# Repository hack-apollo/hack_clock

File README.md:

HACK LABS MatrixClock : https://www.youtube.com/watch?v=k0h2WS6Prsc&t=33s                                                                                
Author: HACK实验室                                                                                     
YouTube ID: HACK实验室, welcome to subscribe https://www.youtube.com/c/HACK实验室                                                        
HACK_CLOCK is a free download and may be used, modified, evaluated and
distributed without charge provided the user adheres to version three of the GNU
General Public License (GPL) and does not remove the copyright notice or this
text.  The GPL V3 text is available on the gnu.org web site
作者：HACK实验室                                                                                        
B站ID：HACK实验室  欢迎订阅 https://space.bilibili.com/395145107                                                                            
微信公众号：HACK实验室，开源资料唯一发布点，定期分享开源硬件以及有价值的技术文章，欢迎关注.

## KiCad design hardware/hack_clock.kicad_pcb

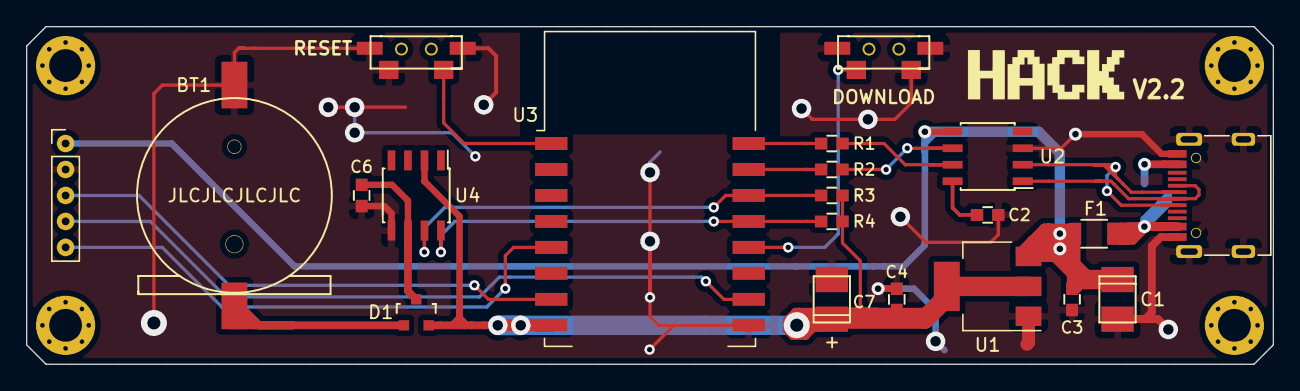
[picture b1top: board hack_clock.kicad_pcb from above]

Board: 2 copper layers, 96.0 x 26.0 mm, 23 parts (1 on the bottom side), 20 nets.

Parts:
BT1: BATTERY(M); CR1220-SMD
C1, C7: 100uF; TantalC_SizeT_3528
C2, C6: 0.1uF; 0603_C
C3, C4: 1uF; 0603_C
D1: BAT54C; SOT-23
F1: FUSE*; F_1206
J1: Conn_01x05_Male; PinHeader_1x05_P2.00mm_Vertical
J2: Jack-DC; BarrelJack_DCDC-SMT
P3: USB_C_Plug_USB2.0; USB-Type-C-NEW
P665: CON_1; CON1
R1, R2: RES(M); 0603_R
R3, R4: 10K; 0603_R
SW1, SW2: switch; SWITCH_PUSH
U1: AMS1117; SOT-223-3_TabPin2
U2: CH340N; SOP-8
U3: ESP-12; ESP-12S
U4: DS3231MZ+; SOP-8

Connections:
+3V3: C4.2, C7.1, D1.2, R3.2, R4.2, U1.2, U3.8, U4.2
+5V: C1.1, C3.2, F1.2, J1.1, U1.3, U2.5
/CLK: J1.5, U3.5
/CS: J1.4, U3.16
/DIN: J1.3, U3.7
/RXD: R1.2, U3.22
/SCL: R4.1, U3.19, U4.8
/SDA: R3.1, U3.20, U4.7
/TXD: R2.2, U3.21
/USB_D+: P3.A6, U2.1
/USB_D-: P3.A7, U2.2
GND: BT1.2, C1.2, C2.1, C3.1, C4.1, C6.1, C7.2, J1.2, J2.2, P3.A1, P3.S1, SW1.1, SW2.1, U1.1, U2.3, U3.15, U4.5
unnamed: BT1.1, D1.1
unnamed: C2.2, U2.8
unnamed: C6.2, D1.3, U4.6
unnamed: F1.1, J2.1, P3.A4
unnamed: R1.1, U2.7
unnamed: R2.1, U2.6
unnamed: SW1.2, U3.1
unnamed: SW2.2, U3.18

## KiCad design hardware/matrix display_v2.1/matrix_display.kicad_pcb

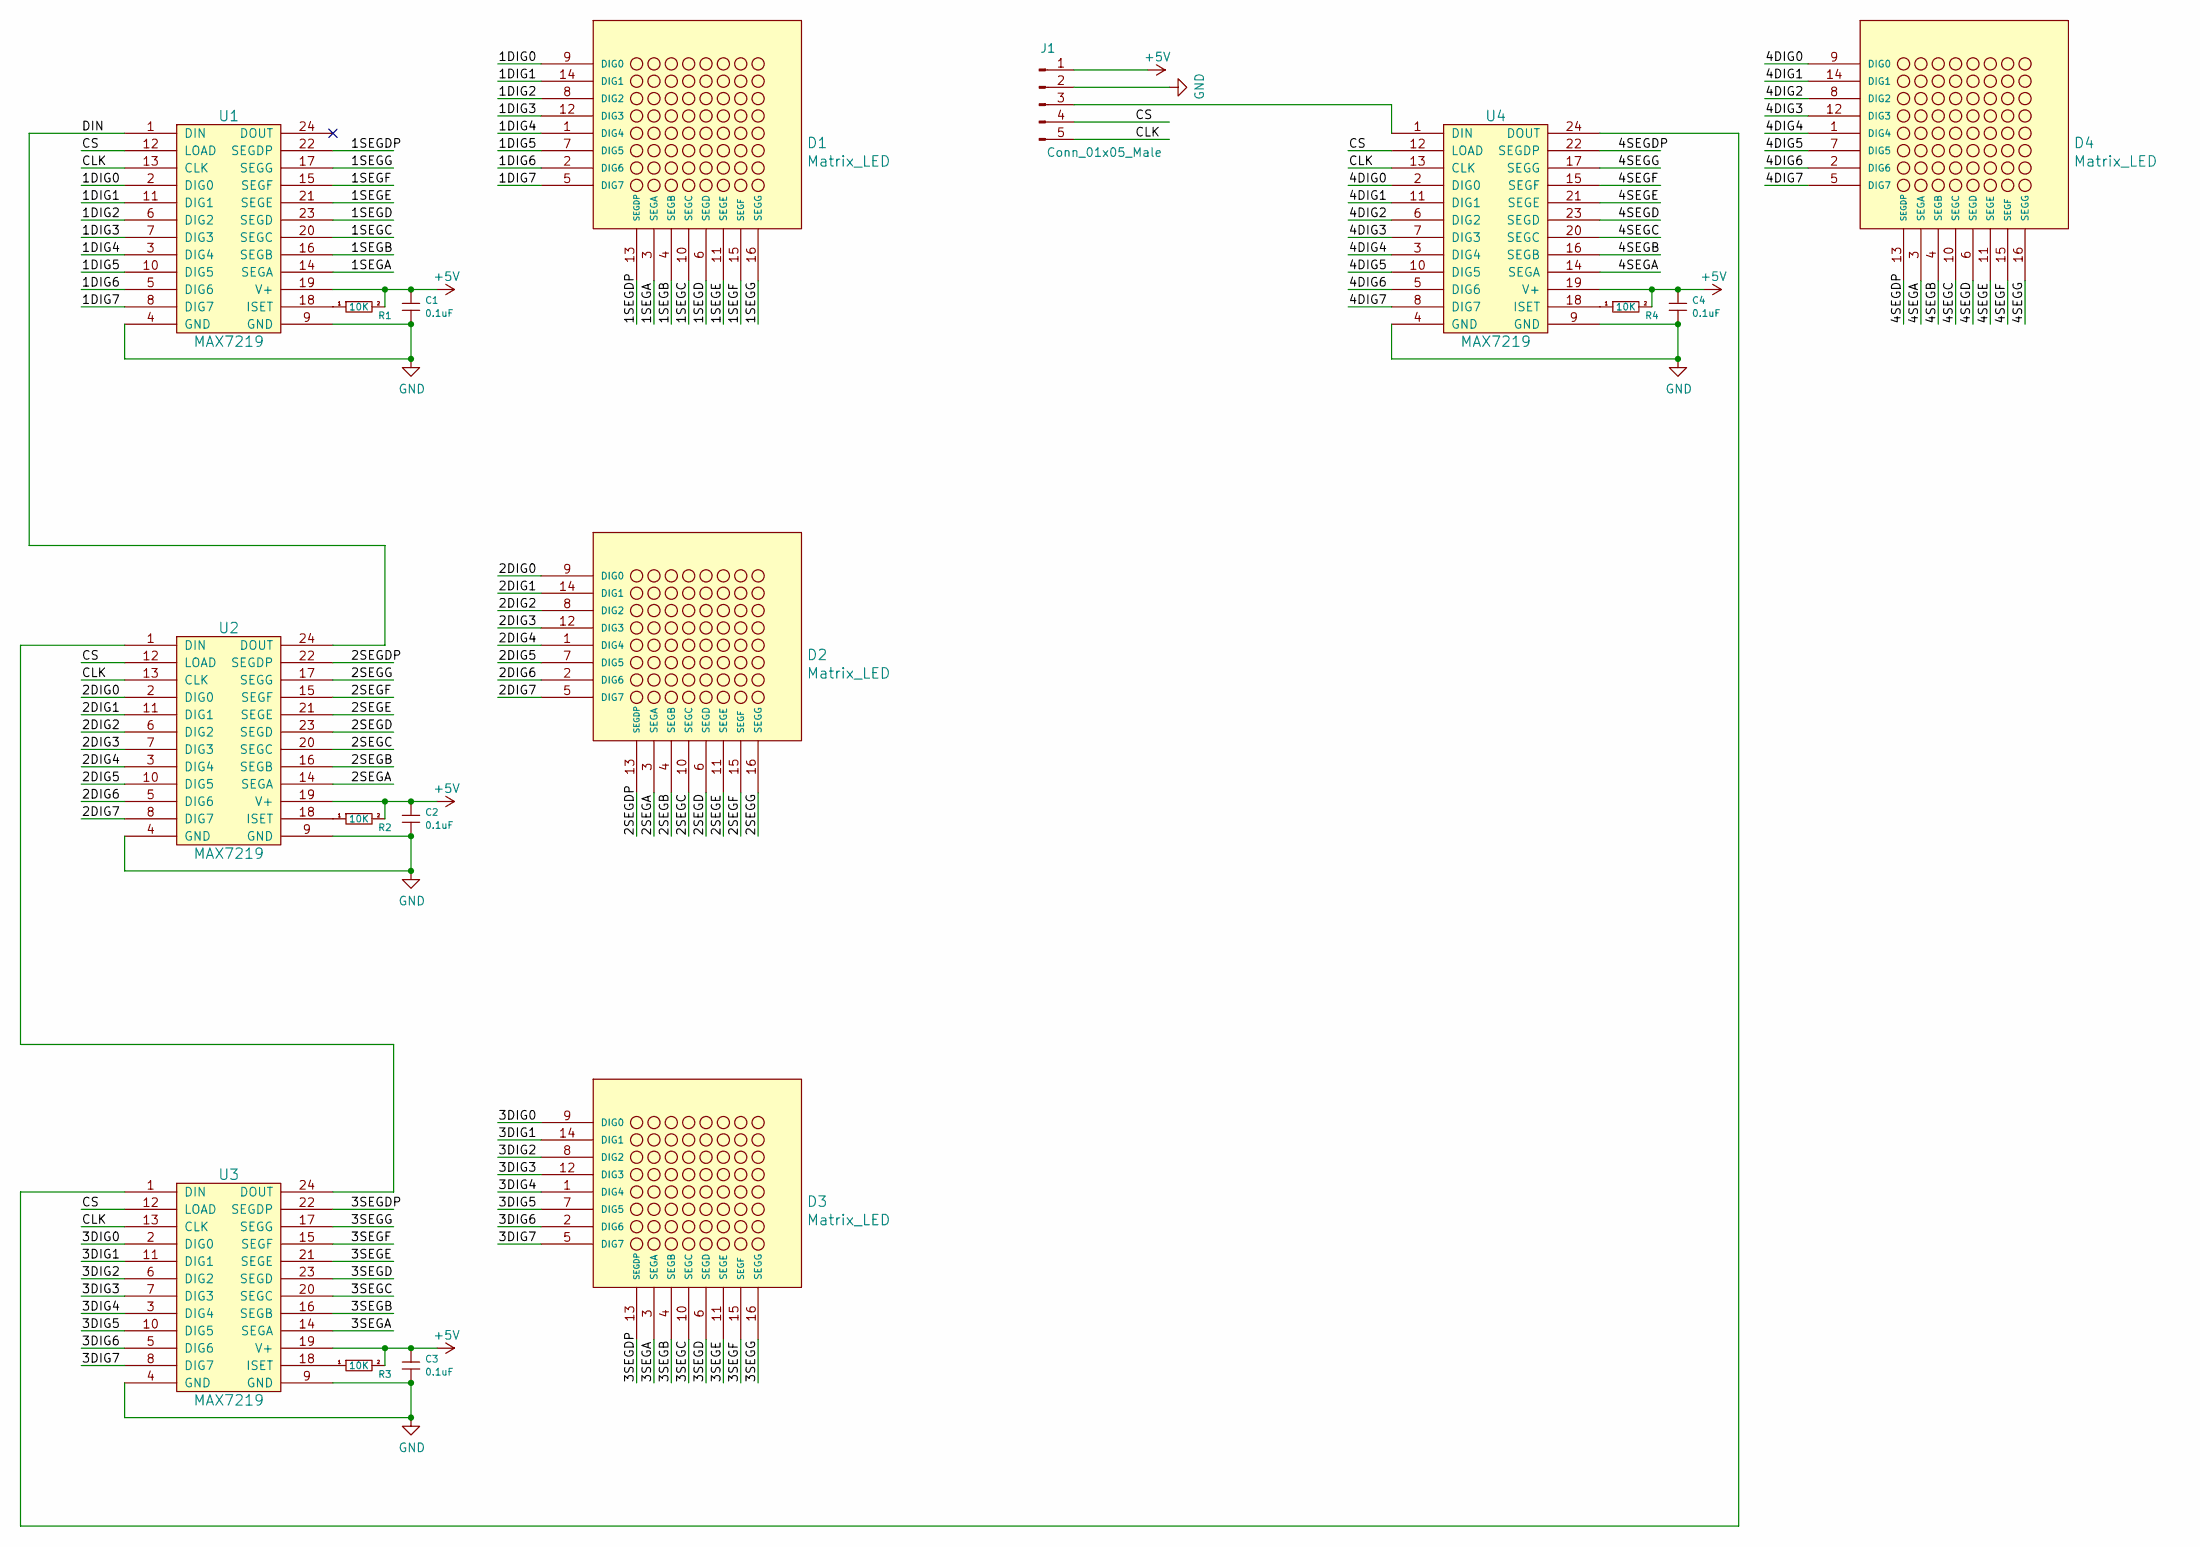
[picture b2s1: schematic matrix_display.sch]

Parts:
C1, C2, C3, C4: 0.1uF; 0603_C
D1, D2, D3, D4: Matrix_LED
J1: Conn_01x05_Male; PinHeader_1x05_P2.00mm_Vertical
R1, R2, R3, R4: 10K; 0603_R
U1, U2, U3, U4: MAX7219; SOIC-24W_7.5x15.4mm_P1.27mm

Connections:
+5V: C1.1, C2.1, C3.1, C4.1, J1.1, R1.2, R2.2, R3.2, R4.2, U1.19 (V+), U2.19 (V+), U3.19 (V+), U4.19 (V+)
/1DIG0: D1.9 (DIG0), U1.2 (DIG0)
/1DIG1: D1.14 (DIG1), U1.11 (DIG1)
/1DIG2: D1.8 (DIG2), U1.6 (DIG2)
/1DIG3: D1.12 (DIG3), U1.7 (DIG3)
/1DIG4: D1.1 (DIG4), U1.3 (DIG4)
/1DIG5: D1.7 (DIG5), U1.10 (DIG5)
/1DIG6: D1.2 (DIG6), U1.5 (DIG6)
/1DIG7: D1.5 (DIG7), U1.8 (DIG7)
/1SEGA: D1.3 (SEGA), U1.14 (SEGA)
/1SEGB: D1.4 (SEGB), U1.16 (SEGB)
/1SEGC: D1.10 (SEGC), U1.20 (SEGC)
/1SEGD: D1.6 (SEGD), U1.23 (SEGD)
/1SEGDP: D1.13 (SEGDP), U1.22 (SEGDP)
/1SEGE: D1.11 (SEGE), U1.21 (SEGE)
/1SEGF: D1.15 (SEGF), U1.15 (SEGF)
/1SEGG: D1.16 (SEGG), U1.17 (SEGG)
/2DIG0: D2.9 (DIG0), U2.2 (DIG0)
/2DIG1: D2.14 (DIG1), U2.11 (DIG1)
/2DIG2: D2.8 (DIG2), U2.6 (DIG2)
/2DIG3: D2.12 (DIG3), U2.7 (DIG3)
/2DIG4: D2.1 (DIG4), U2.3 (DIG4)
/2DIG5: D2.7 (DIG5), U2.10 (DIG5)
/2DIG6: D2.2 (DIG6), U2.5 (DIG6)
/2DIG7: D2.5 (DIG7), U2.8 (DIG7)
/2SEGA: D2.3 (SEGA), U2.14 (SEGA)
/2SEGB: D2.4 (SEGB), U2.16 (SEGB)
/2SEGC: D2.10 (SEGC), U2.20 (SEGC)
/2SEGD: D2.6 (SEGD), U2.23 (SEGD)
/2SEGDP: D2.13 (SEGDP), U2.22 (SEGDP)
/2SEGE: D2.11 (SEGE), U2.21 (SEGE)
/2SEGF: D2.15 (SEGF), U2.15 (SEGF)
/2SEGG: D2.16 (SEGG), U2.17 (SEGG)
/3DIG0: D3.9 (DIG0), U3.2 (DIG0)
/3DIG1: D3.14 (DIG1), U3.11 (DIG1)
/3DIG2: D3.8 (DIG2), U3.6 (DIG2)
/3DIG3: D3.12 (DIG3), U3.7 (DIG3)
/3DIG4: D3.1 (DIG4), U3.3 (DIG4)
/3DIG5: D3.7 (DIG5), U3.10 (DIG5)
/3DIG6: D3.2 (DIG6), U3.5 (DIG6)
/3DIG7: D3.5 (DIG7), U3.8 (DIG7)
/3SEGA: D3.3 (SEGA), U3.14 (SEGA)
/3SEGB: D3.4 (SEGB), U3.16 (SEGB)
/3SEGC: D3.10 (SEGC), U3.20 (SEGC)
/3SEGD: D3.6 (SEGD), U3.23 (SEGD)
/3SEGDP: D3.13 (SEGDP), U3.22 (SEGDP)
/3SEGE: D3.11 (SEGE), U3.21 (SEGE)
/3SEGF: D3.15 (SEGF), U3.15 (SEGF)
/3SEGG: D3.16 (SEGG), U3.17 (SEGG)
/4DIG0: D4.9 (DIG0), U4.2 (DIG0)
/4DIG1: D4.14 (DIG1), U4.11 (DIG1)
/4DIG2: D4.8 (DIG2), U4.6 (DIG2)
/4DIG3: D4.12 (DIG3), U4.7 (DIG3)
/4DIG4: D4.1 (DIG4), U4.3 (DIG4)
/4DIG5: D4.7 (DIG5), U4.10 (DIG5)
/4DIG6: D4.2 (DIG6), U4.5 (DIG6)
/4DIG7: D4.5 (DIG7), U4.8 (DIG7)
/4SEGA: D4.3 (SEGA), U4.14 (SEGA)
/4SEGB: D4.4 (SEGB), U4.16 (SEGB)
/4SEGC: D4.10 (SEGC), U4.20 (SEGC)
/4SEGD: D4.6 (SEGD), U4.23 (SEGD)
/4SEGDP: D4.13 (SEGDP), U4.22 (SEGDP)
/4SEGE: D4.11 (SEGE), U4.21 (SEGE)
/4SEGF: D4.15 (SEGF), U4.15 (SEGF)
/4SEGG: D4.16 (SEGG), U4.17 (SEGG)
/CLK: J1.5, U1.13 (CLK), U2.13 (CLK), U3.13 (CLK), U4.13 (CLK)
/CS: J1.4, U1.12 (LOAD), U2.12 (LOAD), U3.12 (LOAD), U4.12 (LOAD)
/DIN: U1.1 (DIN), U2.24 (DOUT)
GND: C1.2, C2.2, C3.2, C4.2, J1.2, U1.4 (GND), U1.9 (GND), U2.4 (GND), U2.9 (GND), U3.4 (GND), U3.9 (GND), U4.4 (GND), U4.9 (GND)
unnamed: J1.3, U4.1 (DIN)
unnamed: R1.1, U1.18 (ISET)
unnamed: R2.1, U2.18 (ISET)
unnamed: R3.1, U3.18 (ISET)
unnamed: R4.1, U4.18 (ISET)
unnamed: U2.1 (DIN), U3.24 (DOUT)
unnamed: U3.1 (DIN), U4.24 (DOUT)

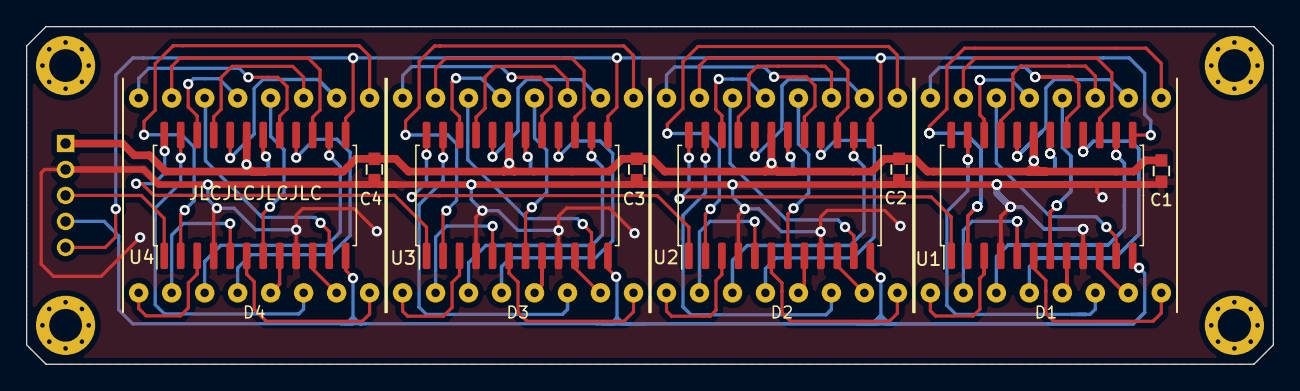
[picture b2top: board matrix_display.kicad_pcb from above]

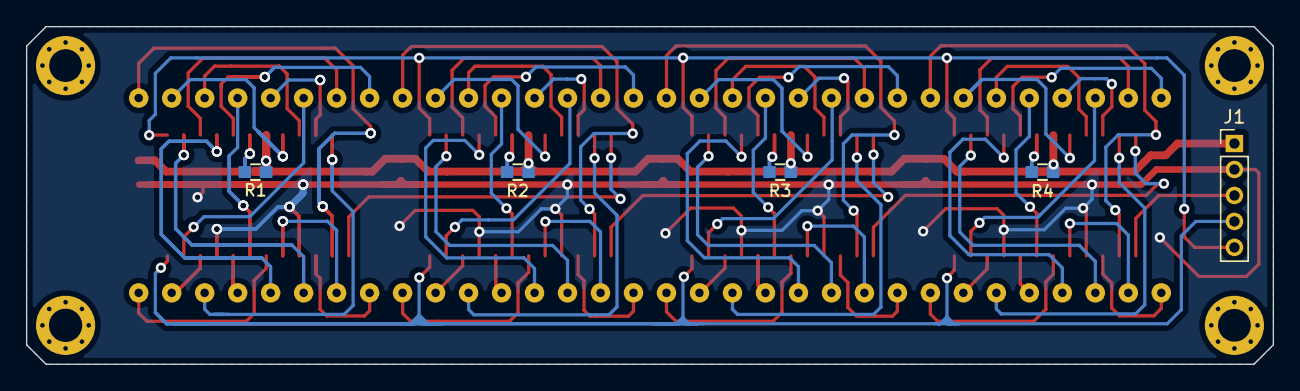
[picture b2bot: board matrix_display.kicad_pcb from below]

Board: 2 copper layers, 96.0 x 26.0 mm, 17 parts (5 on the bottom side), 76 nets.

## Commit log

2020-10-15 first push
2021-03-23 add images
